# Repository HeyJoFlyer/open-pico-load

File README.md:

# Raspberry Pi Pico Open Source DC Load with OLED Display

This project is an open-source DC load built using a Raspberry Pi Pico microcontroller and an OLED display. It allows users to simulate different loads on power sources, to monitor voltage, current, and power, and display them on an OLED screen.

## Features

- Simulate various loads on DC power sources.
- Measure voltage, current, and other parameters.
- Display real-time data on an OLED screen.
- Open-source design using Raspberry Pi Pico.
- Mine does a maximum 36V and around 7A, max power around 100W
- Handsolderable THT components only
- No exact size or spec requirements for components

## Requirements

- Raspberry Pi Pico microcontroller with circuitpython (you can use the one provided in this repo, i would recommend downloading the newest `.uf2`file from [here](https://circuitpython.org/board/raspberry_pi_pico/)) A Raspberry Pi Pico W will work as well, but would be wasted!
- OLED SSD 1306
- Rotary Encoder
- Big Power Resistor
- 2 Mosfets
- Big Mosfet Heatsink
- 5V Linear Regulator
- Resistors, capacitors, diodes and other electronic components (refer to the schematic or for details) The values are just **approximate**! Your values will **limit the maximum voltage** for the voltage dividers as the Raspberry Pi Pico has a max ADC voltage of 3,3V. The capacitor choice will also affect the maximum input voltage.
- Soldering iron and solder
- PCB (from JLCPCB, PCBWAY or other manufactures, I got mine for 5€)

## Installation

1. `git clone https://github.com/HeyJoFlyer/open-pico-load.git`.

1. Connect the components based on the schematic provided (`schematic.svg`).

1. Flash the Circuitpython firmware onto the Raspberry Pi Pico.

1. Upload the code and the libraries (which only work for Circuipython 8.x) to the Pico with the file explorer.

## Usage

1. Connect the Board to a DC power source (7-25V, assuming your fan supports that voltage).

1. Connect your load you want to observe using the screw terminal or solder it directly.

1. Adjust the load settings using the rotary encoder.

1. Monitor the voltage, current, and power on the OLED display.

1. Use the load to test different power sources and observe their behavior.

## Contributing

Contributions are welcome! If you'd like to contribute to this project, feel free to fork the repository, make your changes, and submit a pull request.

## License

This project is licensed under the [MIT License](LICENSE).
Circuipython and the libraries included are licensed under the [MIT License](LICENSE).

## Known Bugs (but the load works in real life!):

- The BACK button is not yet implemented in the software
- Current Tracking is not very smooth (I haven't found a good PID alternative in Circuitpython), so the current jumps around a little.
- Circuitpython has a bug with the display driver, so you need to powercycle the board after uploding new `code.py`.
- MOSFETs sometimes blow up (short circuit) if you use to much current or power (I used two active mosfets).

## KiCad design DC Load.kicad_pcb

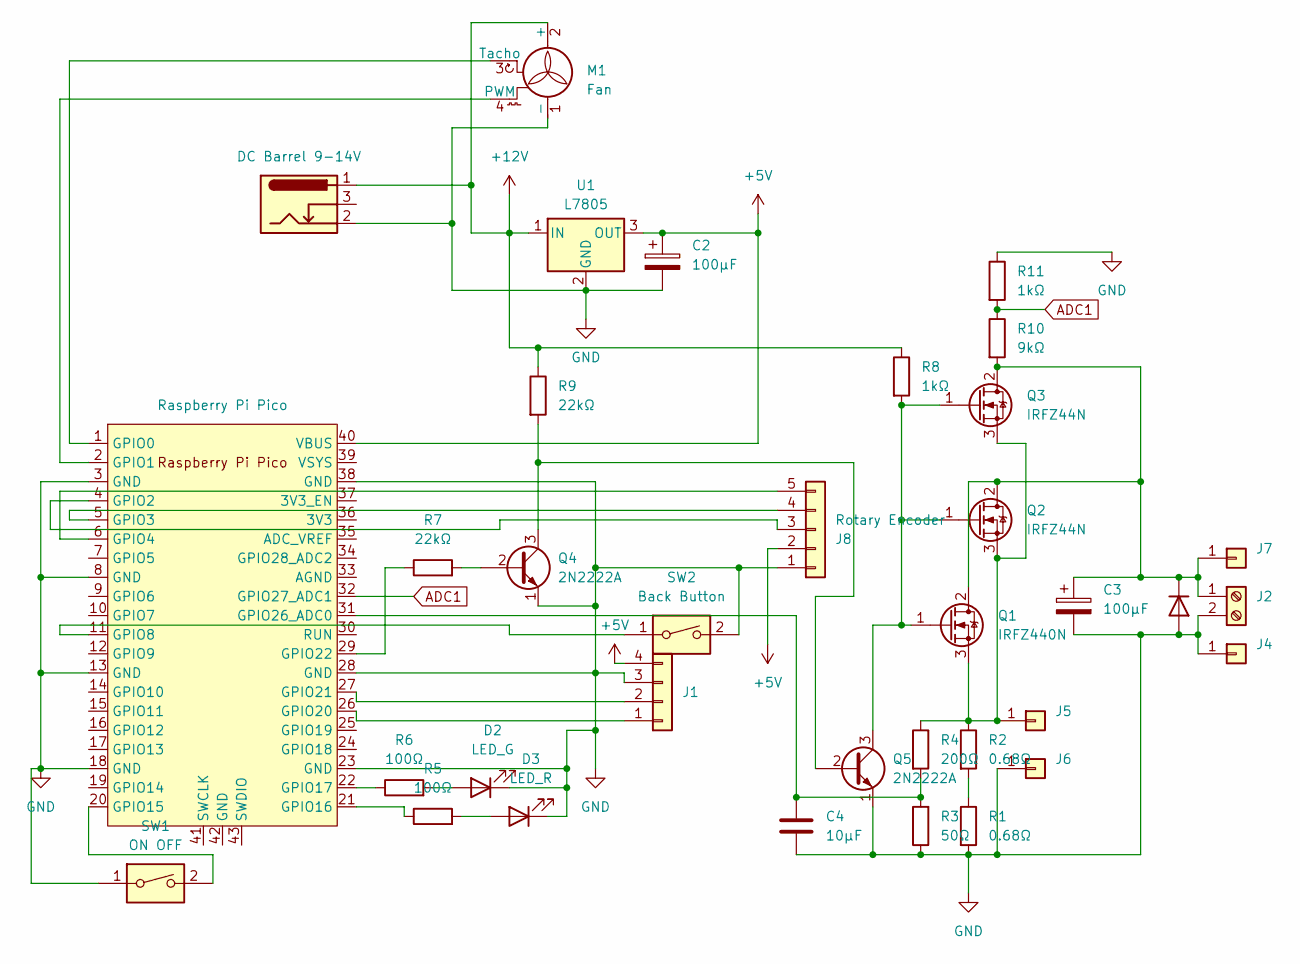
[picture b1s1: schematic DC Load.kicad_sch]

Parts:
C2: 100µF; CP_Radial_D4.0mm_P2.00mm
C3: 100µF; CP_Radial_D8.0mm_P5.00mm
C4: 10µF; CP_Radial_D4.0mm_P2.00mm
D1: 1N4001; D_DO-41_SOD81_P10.16mm_Horizontal
D2: LED_G; LED_D5.0mm
D3: LED_R; LED_D5.0mm
J1: Conn_01x04; PinHeader_1x04_P2.54mm_Vertical
J2: Screw_Terminal_01x02; TerminalBlock_bornier-2_P5.08mm
J3: DC Barrel 9-14V; BarrelJack_Horizontal
J4, J5, J6, J7: Conn_01x01; Pin_D1.3mm_L11.0mm
J8: Rotary Encoder; PinHeader_1x05_P2.54mm_Vertical
M1: Fan; FanPinHeader_1x04_P2.54mm_Vertical
Q1: IRFZ440N; TO-220-3_Vertical
Q2, Q3: IRFZ44N; TO-220-3_Vertical
Q4, Q5: 2N2222A; TO-92_Inline
R1, R2: 0.68Ω
R3: 50Ω; R_Axial_DIN0309_L9.0mm_D3.2mm_P12.70mm_Horizontal
R4: 200Ω; R_Axial_DIN0309_L9.0mm_D3.2mm_P12.70mm_Horizontal
R5, R6: 100Ω; R_Axial_DIN0309_L9.0mm_D3.2mm_P12.70mm_Horizontal
R7, R9: 22kΩ; R_Axial_DIN0309_L9.0mm_D3.2mm_P12.70mm_Horizontal
R8, R11: 1kΩ; R_Axial_DIN0309_L9.0mm_D3.2mm_P12.70mm_Horizontal
R10: 9kΩ; R_Axial_DIN0309_L9.0mm_D3.2mm_P12.70mm_Horizontal
SW1: ON OFF; SW_PUSH_6mm
SW2: Back Button; SW_PUSH_6mm
U1: L7805; TO-220-3_Vertical
U2: Raspberry Pi Pico; RPi_Pico_SMD_TH

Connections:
+5V: C2.1, J1.4, J8.2, U1.3 (OUT), U2.40 (VBUS)
+12V: J3.1, M1.2 (+), R8.1, R9.1, U1.1 (IN)
ADC1: R10.1, R11.2, U2.32 (GPIO27_ADC1)
GND: C2.2, C3.2, C4.2, D1.2 (A), D2.1 (K), D3.1 (K), J1.3, J2.2, J3.2, J4.1, J6.1, J8.1, M1.1 (-), Q4.1 (E), Q5.1 (E), R1.2, R3.1, R11.1, SW1.1, SW2.2, U1.2 (GND), U2.3 (GND), U2.8 (GND), U2.13 (GND), U2.18 (GND), U2.23 (GND), U2.28 (GND), U2.38 (GND)
unnamed: C3.1, D1.1 (K), J2.1, J7.1, Q1.2 (D), Q2.2 (D), Q3.2 (D), R10.2
unnamed: D2.2 (A), R6.2
unnamed: D3.2 (A), R5.2
unnamed: J1.1, U2.26 (GPIO20)
unnamed: J1.2, U2.27 (GPIO21)
unnamed: J5.1, Q1.3 (S), Q2.3 (S), Q3.3 (S), R2.1, R4.1
unnamed: J8.3, U2.4 (GPIO2)
unnamed: J8.4, U2.5 (GPIO3)
unnamed: J8.5, U2.6 (GPIO4)
unnamed: M1.4 (PWM), U2.2 (GPIO1)
unnamed: M1.3 (Tacho), U2.1 (GPIO0)
unnamed: Q1.1 (G), Q2.1 (G), Q3.1 (G), Q5.3 (C), R8.2
unnamed: Q4.2 (B), R7.2
unnamed: Q4.3 (C), Q5.2 (B), R9.2
unnamed: R1.1, R2.2
unnamed: SW2.1, U2.11 (GPIO8)
unnamed: SW1.2, U2.20 (GPIO15)
unnamed: R5.1, U2.21 (GPIO16)
unnamed: R6.1, U2.22 (GPIO17)
unnamed: R7.1, U2.29 (GPIO22)
unnamed: C4.1, R3.2, R4.2, U2.31 (GPIO26_ADC0)

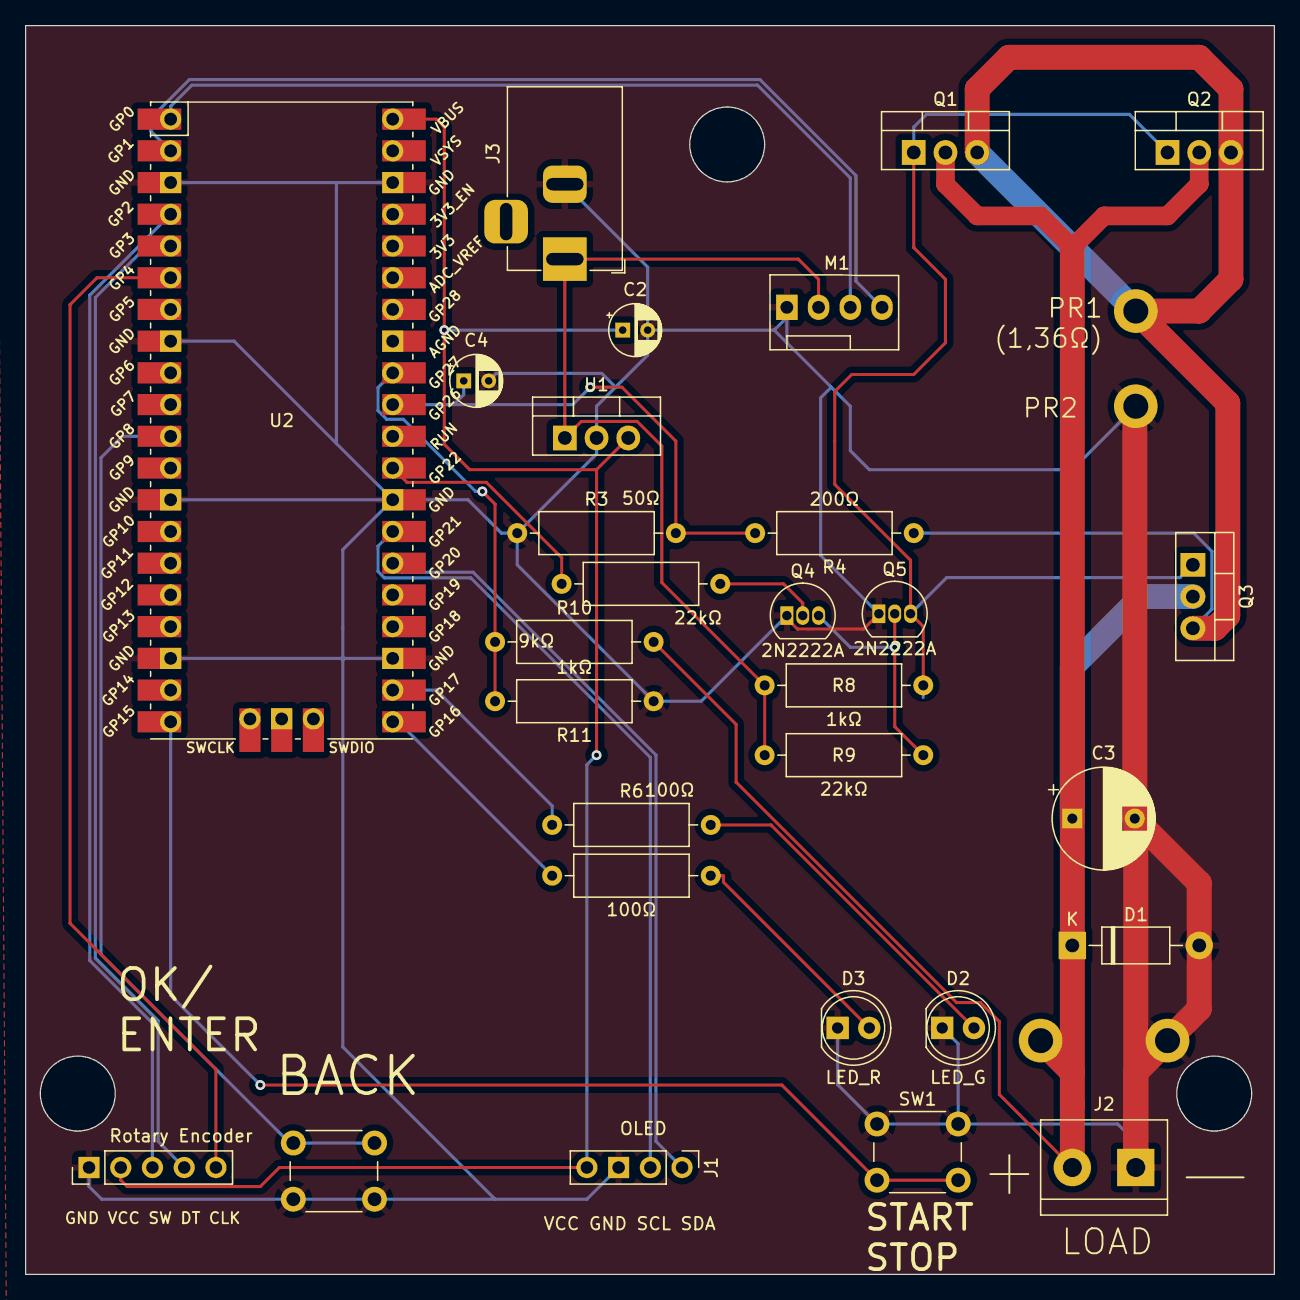
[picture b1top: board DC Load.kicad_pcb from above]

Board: 2 copper layers, 100.0 x 100.0 mm, 33 parts (0 on the bottom side), 24 nets.

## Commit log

2023-12-17 renamed schematic
2023-12-28 Added logging
